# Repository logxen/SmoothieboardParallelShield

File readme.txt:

Smoothieboard Parallel Shield

Licensed under the CERN Open Hardware License version 1.2

This pcb makes connecting a Parallel CNC Machine and the common Reprap Discount GLCD Screen to a Smoothieboard very easy. It has an optional footprint for a 5V regulator to make sure the screen gets enough power. Information on how to configure Smoothieware for use with a display panel can be found here: http://smoothieware.org/panel

Bill of Materials:

1x DB25 R/A PTH connector (such as TE Connectivity 1734350-1)
3x TXS0108E level shifter ic (or 3x 0R 0603 8 resistor networks)
2x SK310A (or similar) SMA schottky diodes to protect voltage inputs from reverse flow
8x 0.1uF 0603 capacitors
1x R78E5.0-0.5 switching voltage regulator
2x 2x5 0.1" shrouded male header
1x 1x3 0.1" male breakaway header
1x 0.1" jumper
2x 2x3 0.1" female header
2x 1x3 0.1" female header
6x 1x4 0.1" female header
1x 1x5 0.1" female header
1x 1x6 0.1" stacking female header (or just a 1x3 female header)

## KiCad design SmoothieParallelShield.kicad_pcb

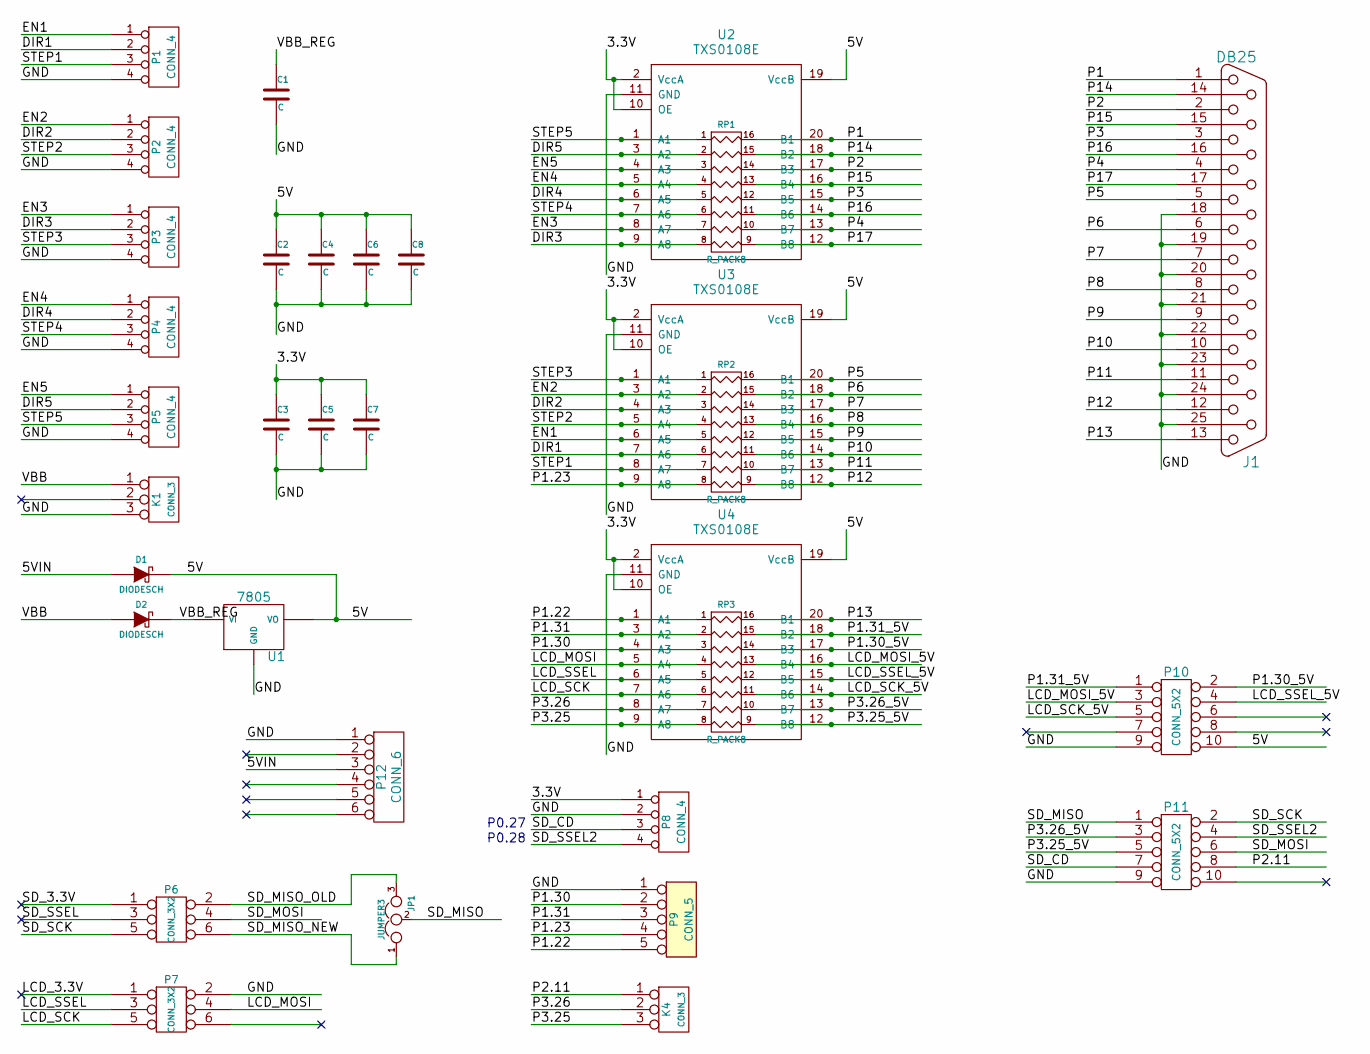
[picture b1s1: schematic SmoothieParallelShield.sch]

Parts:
C1, C2, C3, C4, C5, C6, C7, C8: C
D1, D2: DIODESCH
J1: DB25
JP1: JUMPER3
K1, K4: CONN_3
P1, P2, P3, P4, P5, P8: CONN_4
P6, P7: CONN_3X2
P9: CONN_5
P10, P11: CONN_5X2
P12: CONN_6
RP1, RP2, RP3: R_PACK8
U1: 7805
U2, U3, U4: TXS0108E

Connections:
/3.3V: C3.1, C5.1, C7.1, P8.1, U2.2 (VccA), U2.10 (OE), U3.2 (VccA), U3.10 (OE), U4.2 (VccA), U4.10 (OE)
/5V: C2.1, C4.1, C6.1, C8.1, D1.2 (K), P10.10, U1.VO, U2.19 (VccB), U3.19 (VccB), U4.19 (VccB)
/5VIN: D1.1 (A), P12.3
/DIR1: P1.2, RP2.6, U3.7 (A6)
/DIR2: P2.2, RP2.3, U3.4 (A3)
/DIR3: P3.2, RP1.8, U2.9 (A8)
/DIR4: P4.2, RP1.5, U2.6 (A5)
/DIR5: P5.2, RP1.2, U2.3 (A2)
/EN1: P1.1, RP2.5, U3.6 (A5)
/EN2: P2.1, RP2.2, U3.3 (A2)
/EN3: P3.1, RP1.7, U2.8 (A7)
/EN4: P4.1, RP1.4, U2.5 (A4)
/EN5: P5.1, RP1.3, U2.4 (A3)
/GND: C1.2, C2.2, C3.2, C4.2, C5.2, C6.2, C7.2, C8.2, J1.18, J1.19, J1.20, J1.21, J1.22, J1.23, J1.24, J1.25, K1.3, P1.4, P2.4, P3.4, P4.4, P5.4, P7.2, P8.2, P9.1, P10.9, P11.9, P12.1, U1.GND, U2.11 (GND), U3.11 (GND), U4.11 (GND)
/LCD_MOSI: P7.4, RP3.4, U4.5 (A4)
/LCD_MOSI_5V: P10.3, RP3.13 (R4), U4.16 (B4)
/LCD_SCK: P7.5, RP3.6, U4.7 (A6)
/LCD_SCK_5V: P10.5, RP3.11 (R6), U4.14 (B6)
/LCD_SSEL: P7.3, RP3.5, U4.6 (A5)
/LCD_SSEL_5V: P10.4, RP3.12 (R5), U4.15 (B5)
/P1: J1.1, RP1.16 (R1), U2.20 (B1)
/P1.22: P9.5, RP3.1, U4.1 (A1)
/P1.23: P9.4, RP2.8, U3.9 (A8)
/P1.30: P9.2, RP3.3, U4.4 (A3)
/P1.30_5V: P10.2, RP3.14 (R3), U4.17 (B3)
/P1.31: P9.3, RP3.2, U4.3 (A2)
/P1.31_5V: P10.1, RP3.15 (R2), U4.18 (B2)
/P2: J1.2, RP1.14 (R3), U2.17 (B3)
/P2.11: K4.1, P11.8
/P3: J1.3, RP1.12 (R5), U2.15 (B5)
/P3.25: K4.3, RP3.8, U4.9 (A8)
/P3.25_5V: P11.5, RP3.9 (R8), U4.12 (B8)
/P3.26: K4.2 (PM), RP3.7, U4.8 (A7)
/P3.26_5V: P11.3, RP3.10 (R7), U4.13 (B7)
/P4: J1.4, RP1.10 (R7), U2.13 (B7)
/P5: J1.5, RP2.16 (R1), U3.20 (B1)
/P6: J1.6, RP2.15 (R2), U3.18 (B2)
/P7: J1.7, RP2.14 (R3), U3.17 (B3)
/P8: J1.8, RP2.13 (R4), U3.16 (B4)
/P9: J1.9, RP2.12 (R5), U3.15 (B5)
/P10: J1.10, RP2.11 (R6), U3.14 (B6)
/P11: J1.11, RP2.10 (R7), U3.13 (B7)
/P12: J1.12, RP2.9 (R8), U3.12 (B8)
/P13: J1.13, RP3.16 (R1), U4.20 (B1)
/P14: J1.14, RP1.15 (R2), U2.18 (B2)
/P15: J1.15, RP1.13 (R4), U2.16 (B4)
/P16: J1.16, RP1.11 (R6), U2.14 (B6)
/P17: J1.17, RP1.9 (R8), U2.12 (B8)
/SD_CD: P8.3, P11.7
/SD_MISO: JP1.2, P11.1
/SD_MISO_NEW: JP1.1, P6.6
/SD_MISO_OLD: JP1.3, P6.2
/SD_MOSI: P6.4, P11.6
/SD_SCK: P6.5, P11.2
/SD_SSEL2: P8.4, P11.4
/STEP1: P1.3, RP2.7, U3.8 (A7)
/STEP2: P2.3, RP2.4, U3.5 (A4)
/STEP3: P3.3, RP2.1, U3.1 (A1)
/STEP4: P4.3, RP1.6, U2.7 (A6)
/STEP5: P5.3, RP1.1, U2.1 (A1)
/VBB: D2.1 (A), K1.1
/VBB_REG: C1.1, D2.2 (K), U1.VI

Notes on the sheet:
P0.27
P0.28

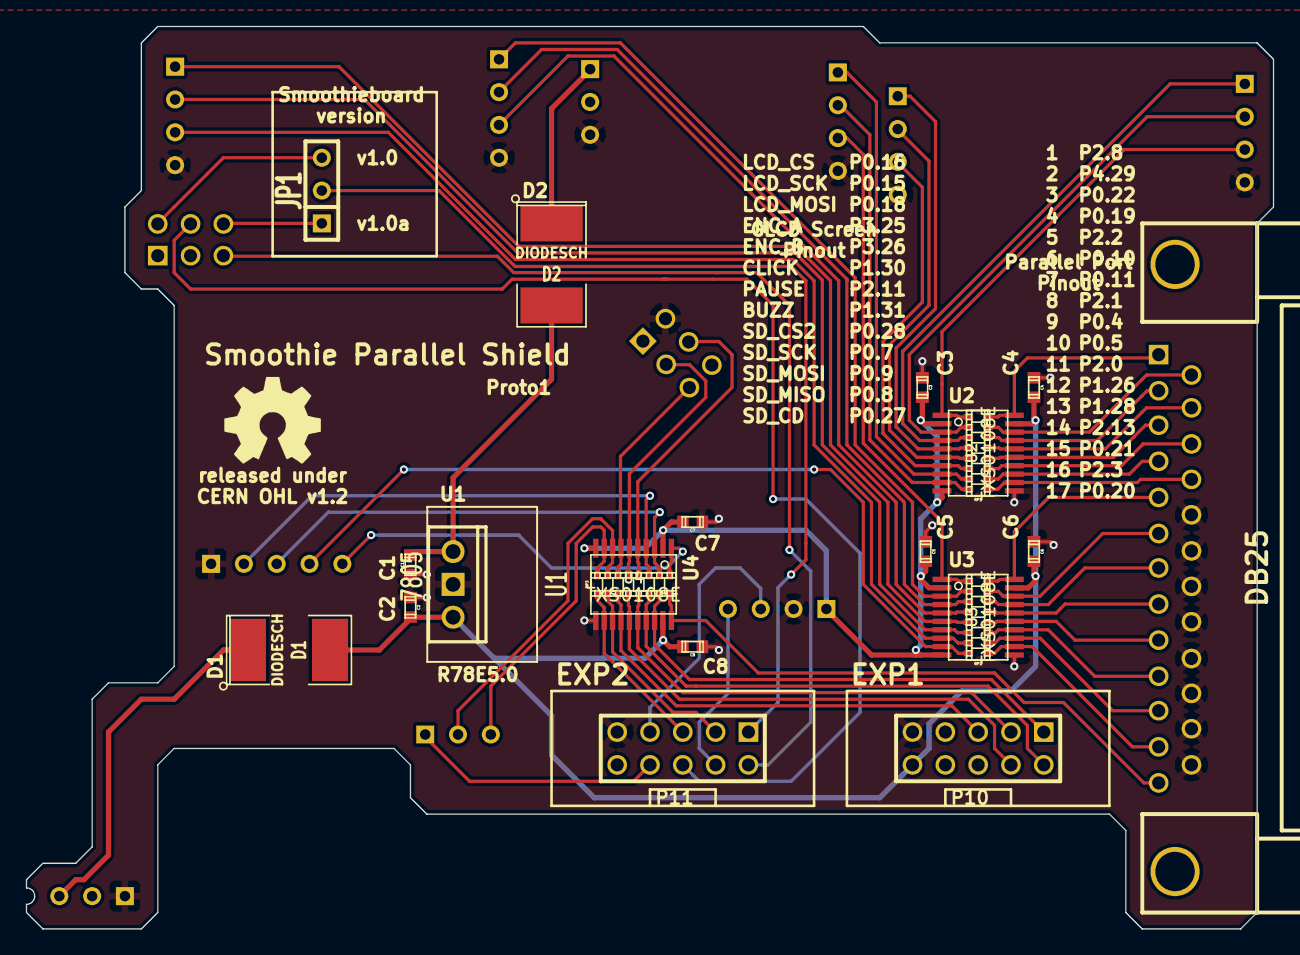
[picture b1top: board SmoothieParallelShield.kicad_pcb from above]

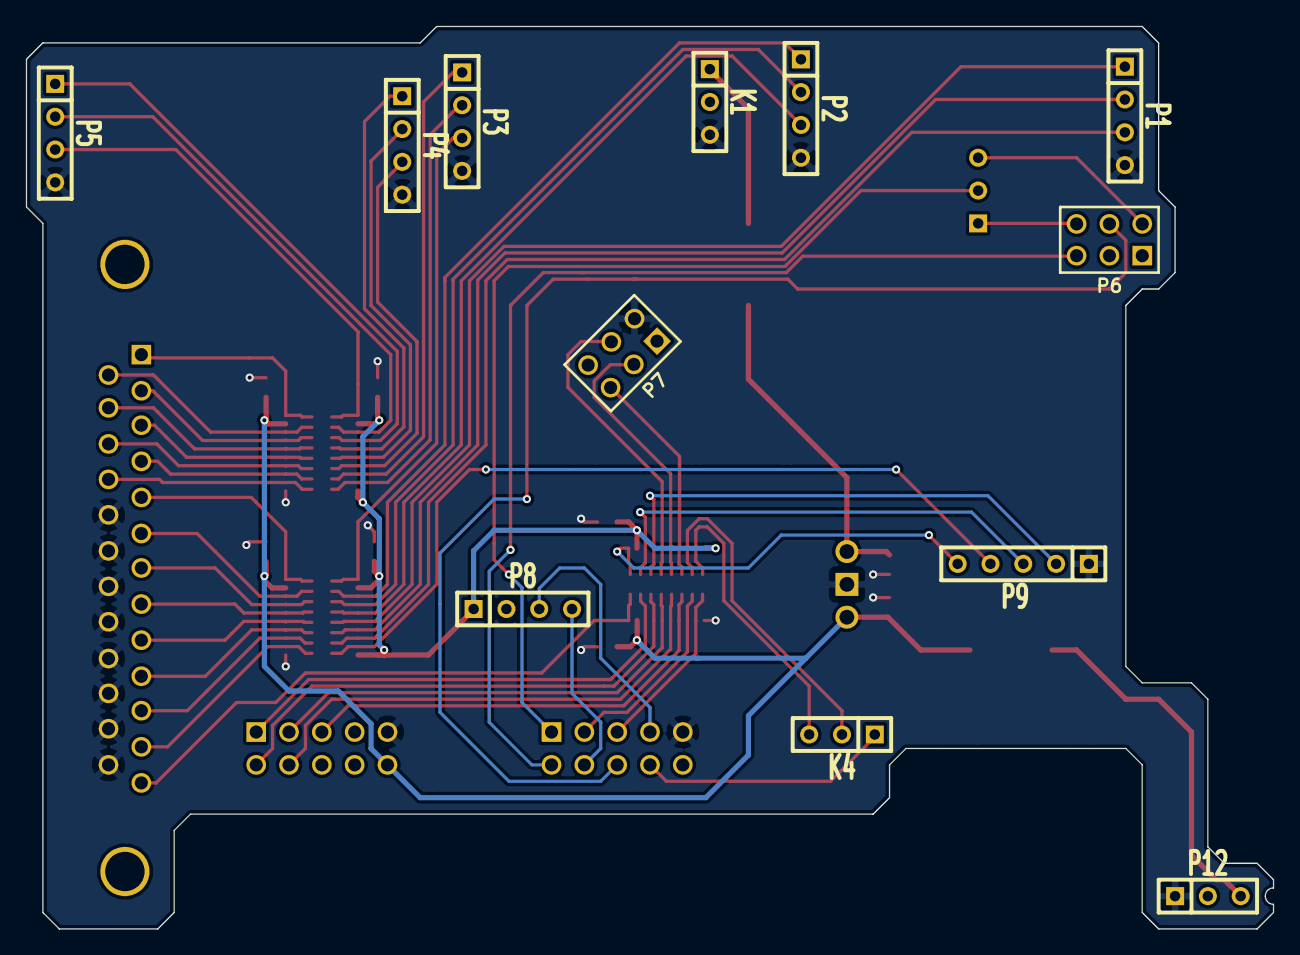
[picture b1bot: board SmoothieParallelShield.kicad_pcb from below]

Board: 2 copper layers, 96.5 x 69.9 mm, 34 parts (12 on the bottom side), 62 nets.

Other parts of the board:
VAL: REF; OSHW-LOGO_SMALL

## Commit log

2014-12-14 :neckbeard: Added .gitattributes
2014-12-14 Proto1
    Initial commit of Proto1 design

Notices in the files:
SmoothieParallelShield.kicad_pcb:
released under
CERN OHL v1.2
